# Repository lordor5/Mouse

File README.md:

# Open Source Wireless Mouse

A custom, high-performance wireless mouse project featuring custom PCB design, high-end optical sensors, and Hall effect switches. This repository contains all hardware schematics, PCB layouts, and firmware source code required to build the mouse from scratch. 

> ⚠️ **WORK IN PROGRESS (WIP) / UNTESTED HARDWARE** ⚠️  
> This project is currently in active development. The custom PCB design and firmware have **not yet been physically tested or manufactured**. The files are provided as-is. Build at your own risk!

## Project Overview

This project is built around the popular Nice!Nano (nRF52840) footprint and uses a combination of modern frameworks like Zephyr for the firmware. The hardware design is fully documented in KiCad and utilizes magnetic Hall effect sensors for durable, debounce-free clicking.

### Key Features

* **Custom KiCad PCB**: Fully routed custom board (`mouse.kicad_pcb`) with production-ready Gerber/BOM files.
* **High-End Optical Sensor**: Utilizes the PAW3395 mouse sensor.
* **Magnetic Switches**: Implements the TLE493DP2B6A2HTSA1 Hall effect sensor for primary buttons.
* **Multi-Environment Firmware**: Codebase includes implementations in Zephyr RTOS.

---

## 🛠️ Hardware & Bill of Materials (BOM)

The hardware relies on readily available components. Below is the core BOM based on the current design:

| Component | Description | Estimated Cost |
| --- | --- | --- |
| **PAW3395** | Primary Mouse Sensor | 10.00€ |
| **TLE493DP2B6A2HTSA1** | Hall Effect Sensor (Switches) | 2.59€ |
| **LDO Regulator** | Power Management | 0.753€ |
| **Nice!Nano** | nRF52840 Microcontroller Board | - |
| **TMAG5170A2QDGKR** | Alternative Magnetic Sensor | - |
| **SSSS811101** | Power Switch | - |

> **Note on Power:** The 2V LDO regulator is required for stable sensor operation and is currently sourced via Mouser, as it is difficult to find on AliExpress.

---

## 📂 Repository Structure

```text
.
├── Code/
│   ├── nrf/                  # Rust-based firmware using nrf-hal (blinky, pwm, i2s, usb)
│   ├── PMW3389DM-master/     # Arduino polling/interrupt examples for the sensor
│   └── zephyr/               # Zephyr RTOS implementation and board overlays
├── Img/                      # Project images and renders (e.g., PCBFront.png)
└── PCB/
    ├── Components/           # Custom KiCad footprints and symbols (.step, .kicad_mod)
    ├── production/           # Manufacturing files (BOM, positions, netlist, zip)
    └── mouse.kicad_pro       # Main KiCad project file

```

---

## 💻 Firmware & Software

This repository offers multiple paths for firmware development depending on your preferred tech stack:

1. **Rust (`Code/nrf`)**: Bare-metal Rust implementation utilizing `embassy` or `nrf-hal` for maximum memory safety and low power consumption (NOT TESTED).
2. **Zephyr RTOS (`Code/zephyr`)**: Includes board overlays (e.g., `nrf52840dk`, `esp32c3`) and HID peripheral configurations for scalable RTOS development (NOT TESTED).
3. **Arduino / ESP32 (`Code/PMW3389DM-master`)**: For rapid prototyping, utilizing the standard ESP32 BLE Mouse library.

### Building the Firmware (Rust)

Navigate to the `Code/nrf` directory and use Cargo to build the project for the `thumbv7em-none-eabi` target:

```bash
cd Code/nrf
cargo build --release

```

---

## 🏭 Manufacturing the PCB

All necessary files to order the PCB from fabricators (like JLCPCB or PCBWay) are located in the `PCB/production/` folder.

* **`mouse.zip`**: Contains the Gerber files.
* **`bom.csv`**: Bill of Materials for SMT assembly.
* **`positions.csv`**: CPL/Pick-and-place files.

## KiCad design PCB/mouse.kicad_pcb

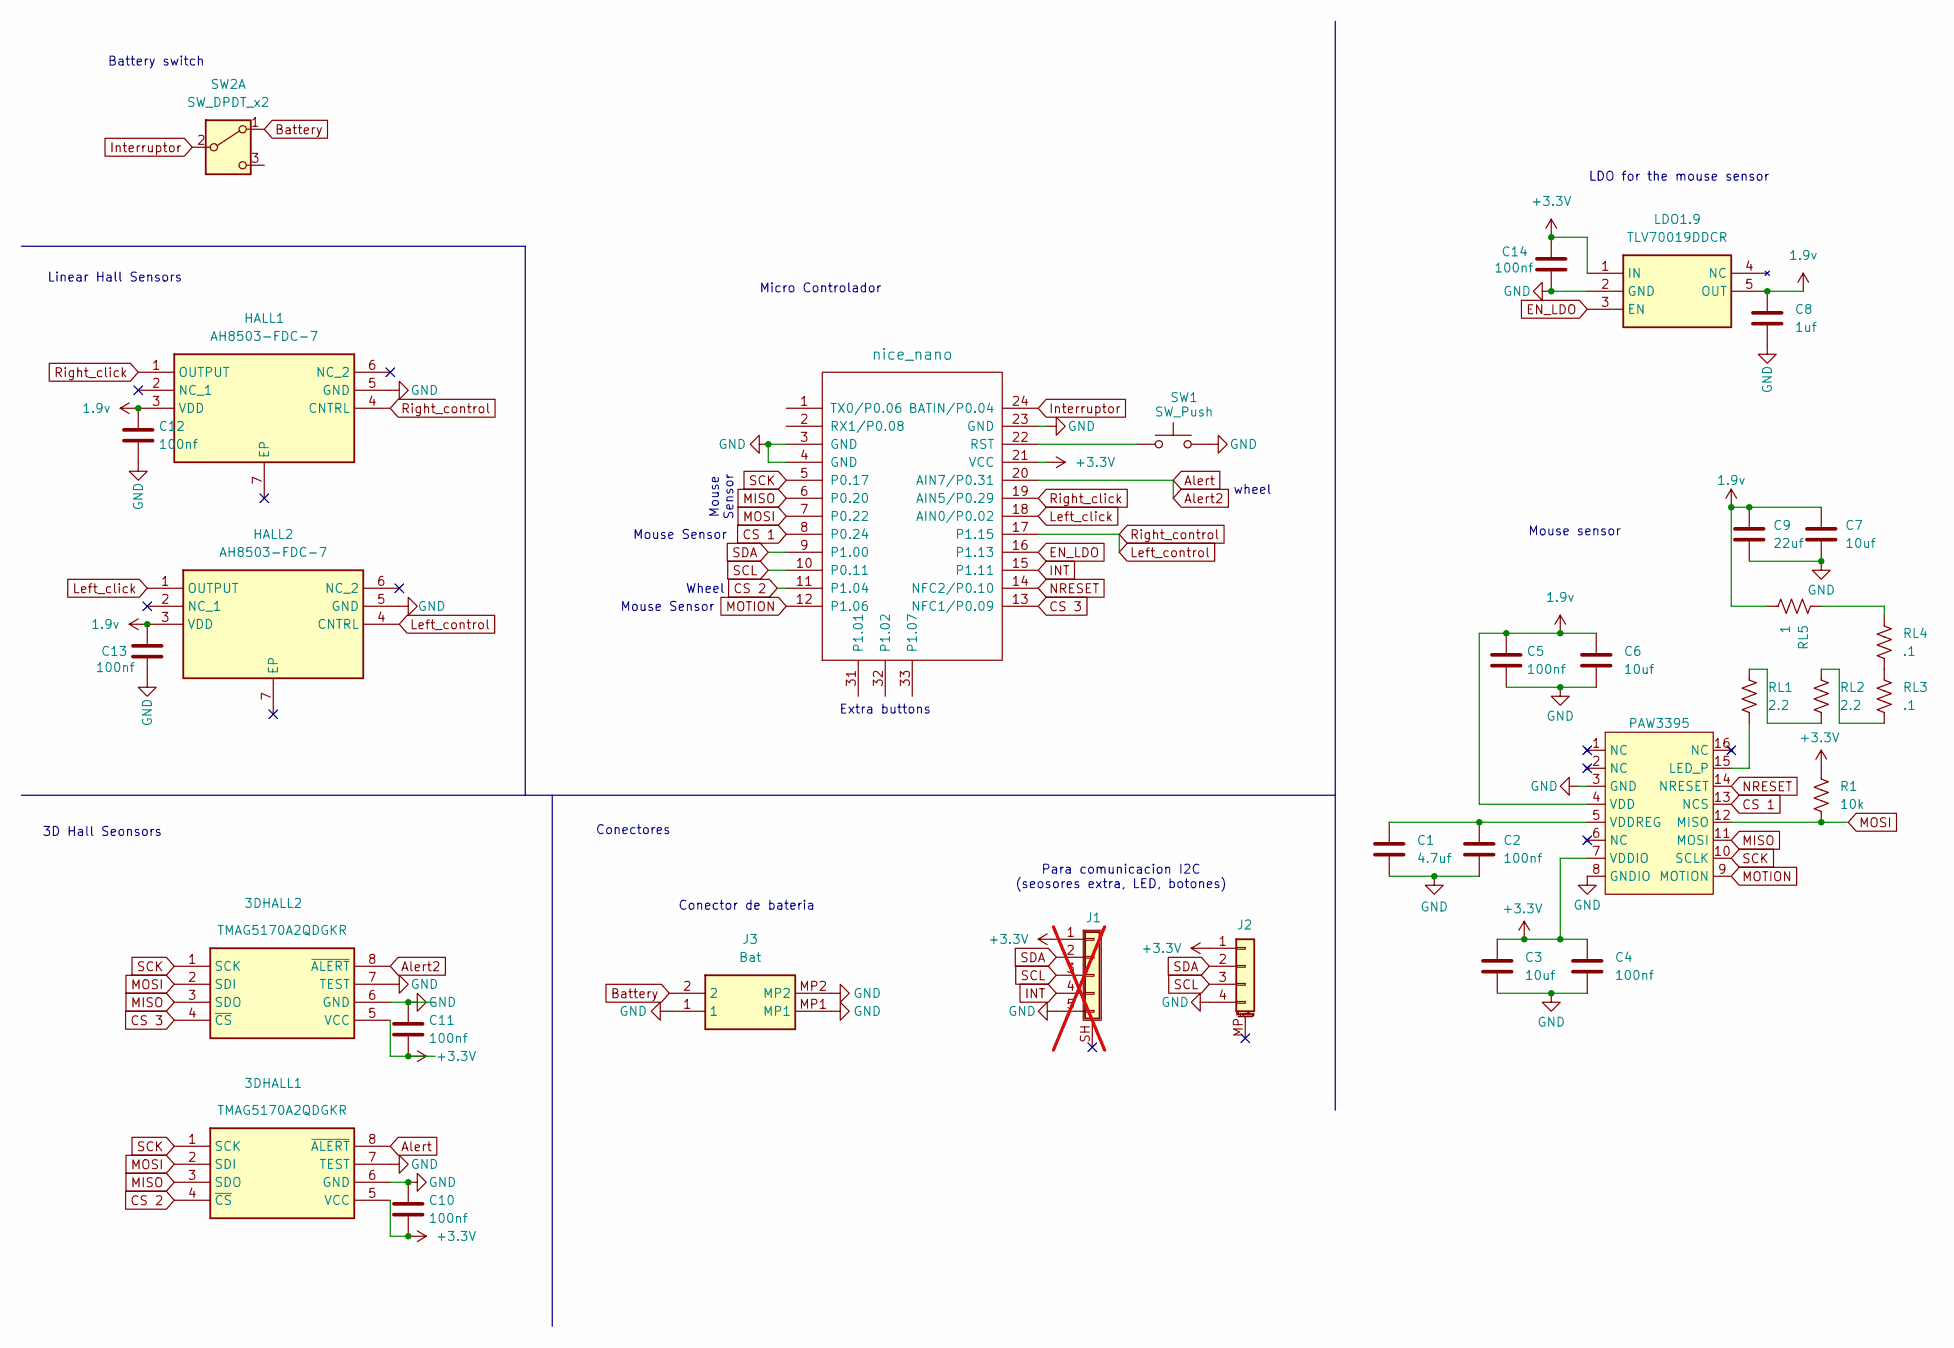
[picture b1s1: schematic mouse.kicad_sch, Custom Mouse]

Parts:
3DHALL1, 3DHALL2: TMAG5170A2QDGKR; SOP65P490X110-8N; Manufacturer_Part_Number TMAG5170A2QDGKR; JLC-PCB C3716101
C1: 4.7uf; C_0805_2012Metric; JLC-PCB C1779
C2, C4, C5, C10, C11, C12, C13, C14: 100nf; C_0805_2012Metric; JLC-PCB C28233
C3, C6, C7: 10uf; C_0805_2012Metric; JLC-PCB C15850
C8: 1uf; C_0805_2012Metric; JLC-PCB C28323
C9: 22uf; C_0805_2012Metric; JLC-PCB C45783
HALL1, HALL2: AH8503-FDC-7; DFN-6-1EP_2x2mm_P0.65mm_EP1.01x1.7mm; Manufacturer_Part_Number AH8503-FDC-7; JLC-PCB C842150
J1: Conn_01x05_Shielded; PinHeader_1x05_P2.54mm_Vertical; not fitted
J2: Conn_01x04_MountingPin; JST_SH_SM04B-SRSS-TB_1x04-1MP_P1.00mm_Horizontal; JLC-PCB C160404
J3: Bat; 532614002; Manufacturer_Part_Number 53261-4002; JLC-PCB C17559503
LDO1.9: TLV70019DDCR; SOT95P280X110-5N; Manufacturer_Part_Number TLV70019DDCR; JLC-PCB C2862411
OpticalSensor1: PAW3395; DIP-16_PAW3395; JLC-PCB C41346211
R1: 10k; R_0805_2012Metric; JLC-PCB C17414
RL1, RL2: 2.2; R_0805_2012Metric; JLC-PCB C17521
RL3, RL4: .1; R_1206_3216Metric; JLC-PCB C25334
RL5: 1; R_0805_2012Metric; JLC-PCB C25271
SW1: SW_Push; SW_TS-1088-AR02016; JLC-PCB C720477
SW2: SW_DPDT_x2; SSSS811101; JLC-PCB C97433
U2: nice_nano

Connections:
1.9v: C5.1, C6.1, C7.1, C8.1, C9.1, C12.1, C13.1, HALL1.3 (VDD), HALL2.3 (VDD), LDO1.9.5 (OUT), OpticalSensor1.4 (VDD), RL5.1
+3.3V: 3DHALL1.5 (VCC), 3DHALL2.5 (VCC), C3.1, C4.1, C10.2, C11.2, C14.1, J1.1, J2.1, LDO1.9.1 (IN), OpticalSensor1.7 (VDDIO), R1.2, U2.21 (VCC)
Alert: 3DHALL1.8 (~ALERT), 3DHALL2.8 (~ALERT), U2.20 (AIN7/P0.31)
Battery: J3.2, SW2.1 (A)
CS 1: OpticalSensor1.13 (NCS), U2.8 (P0.24)
CS 2: 3DHALL1.4 (~CS), U2.11 (P1.04)
CS 3: 3DHALL2.4 (~CS), U2.13 (NFC1/P0.09)
EN_LDO: LDO1.9.3 (EN), U2.16 (P1.13)
GND: 3DHALL1.6 (GND), 3DHALL1.7 (TEST), 3DHALL2.6 (GND), 3DHALL2.7 (TEST), C1.2, C2.2, C3.2, C4.2, C5.2, C6.2, C7.2, C8.2, C9.2, C10.1, C11.1, C12.2, C13.2, C14.2, HALL1.5 (GND), HALL2.5 (GND), J1.5, J2.4, J3.1, J3.MP1, J3.MP2, LDO1.9.2 (GND), OpticalSensor1.3 (GND), OpticalSensor1.8 (GNDIO), SW1.2, U2.3 (GND), U2.4 (GND), U2.23 (GND)
INT: J1.4, U2.15 (P1.11)
Interruptor: SW2.2 (B), U2.24 (BATIN/P0.04)
Left_click: HALL2.1 (OUTPUT), U2.18 (AIN0/P0.02)
Left_control: HALL1.4 (CNTRL), HALL2.4 (CNTRL), U2.17 (P1.15)
MISO: 3DHALL1.3 (SDO), 3DHALL2.3 (SDO), OpticalSensor1.11 (MOSI), U2.6 (P0.20)
MOSI: 3DHALL1.2 (SDI), 3DHALL2.2 (SDI), OpticalSensor1.12 (MISO), R1.1, U2.7 (P0.22)
MOTION: OpticalSensor1.9 (MOTION), U2.12 (P1.06)
NRESET: OpticalSensor1.14 (NRESET), U2.14 (NFC2/P0.10)
unnamed: OpticalSensor1.15 (LED_P), RL1.1
unnamed: C1.1, C2.1, OpticalSensor1.5 (VDDREG)
unnamed: RL1.2, RL2.1
unnamed: RL2.2, RL3.1
unnamed: RL3.2, RL4.1
unnamed: RL4.2, RL5.2
unnamed: SW1.1, U2.22 (RST)
Right_click: HALL1.1 (OUTPUT), U2.19 (AIN5/P0.29)
SCK: 3DHALL1.1 (SCK), 3DHALL2.1 (SCK), OpticalSensor1.10 (SCLK), U2.5 (P0.17)
SCL: J1.3, J2.3, U2.10 (P0.11)
SDA: J1.2, J2.2, U2.9 (P1.00)

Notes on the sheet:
Conector de bateria
Linear Hall Sensors
Mouse Sensor
Mouse Sensor
Para comunicacion I2C (seosores extra, LED, botones)
3D Hall Seonsors
Mouse sensor
Extra buttons
Micro Controlador
Battery switch
Wheel
Conectores
wheel
LDO for the mouse sensor

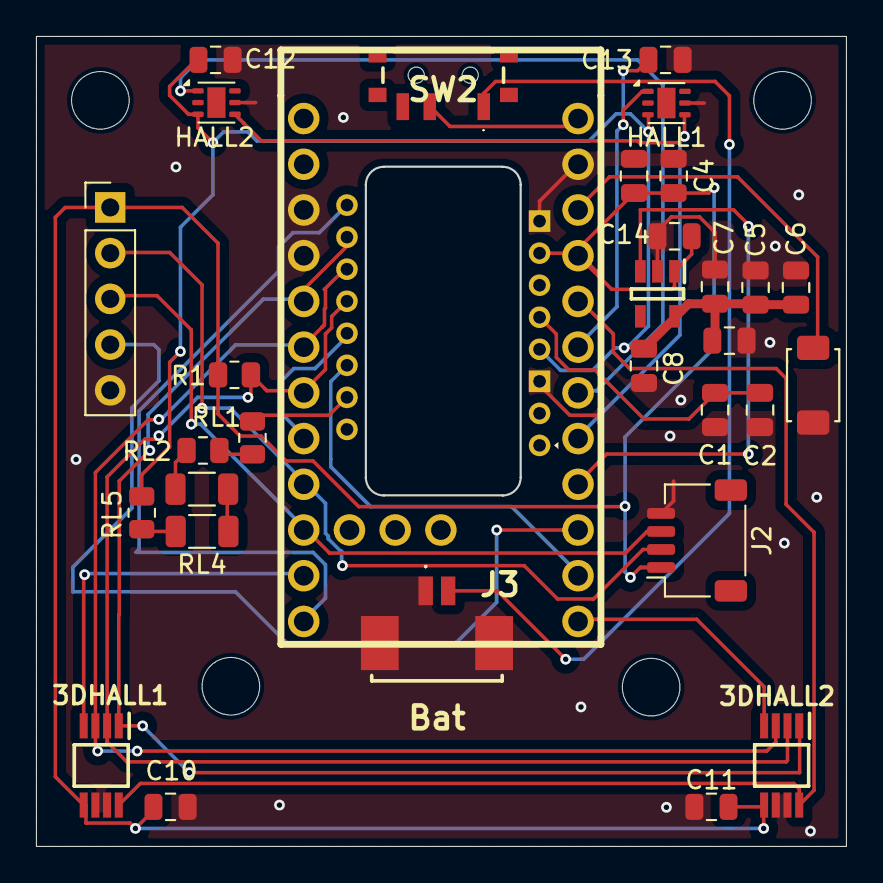
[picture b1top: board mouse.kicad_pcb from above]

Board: 2 copper layers, 44.9 x 44.9 mm, 32 parts (0 on the bottom side), 28 nets.

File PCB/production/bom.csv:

Designator,Footprint,Quantity,Value,LCSC Part #
3DHALL1,SOP65P490X110-8N,1,TMAG5170A2QDGKR,
3DHALL2,SOP65P490X110-8N,1,TMAG5170A2QDGKR,C3716101
C1,0805,1,4.7uf,C1779
"C10, C11, C12, C13, C14",0805,5,100nf,
"C2, C4, C5",0805,3,100nf,C28233
"C3, C6, C7",0805,3,10uf,C15850
C8,0805,1,1uf,C28323
C9,0805,1,22uf,C45783
"HALL1, HALL2",DFN-6-1EP_2x2mm_P0.65mm_EP1.01x1.7mm,2,AH8503-FDC-7,
J2,JST_SH_SM04B-SRSS-TB_1x04-1MP_P1.00mm_Horizontal,1,Conn_01x04_MountingPin,C160404
J3,532614002,1,Bat,C17559503
LDO1.9,SOT95P280X110-5N,1,TLV70019DDCR,C2862411
OPTICALSENSOR1,DIP-16_PAW3395,1,PAW3395,C41346211
R1,0805,1,10k,C17414
"RL1, RL2",0805,2,2.2,C17521
"RL3, RL4",1206,2,.1,
RL5,0805,1,1,C25271
SW1,SW_TS-1088-AR02016,1,SW_Push,C720477
SWITCH1,SSSS811101,1,SSSS811101,C97433
U2,nice_nano,1,nice_nano,

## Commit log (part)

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2024-05-09 Sensor datasheet
2024-05-09 hall effect datasheet
2025-10-28 En proceso
